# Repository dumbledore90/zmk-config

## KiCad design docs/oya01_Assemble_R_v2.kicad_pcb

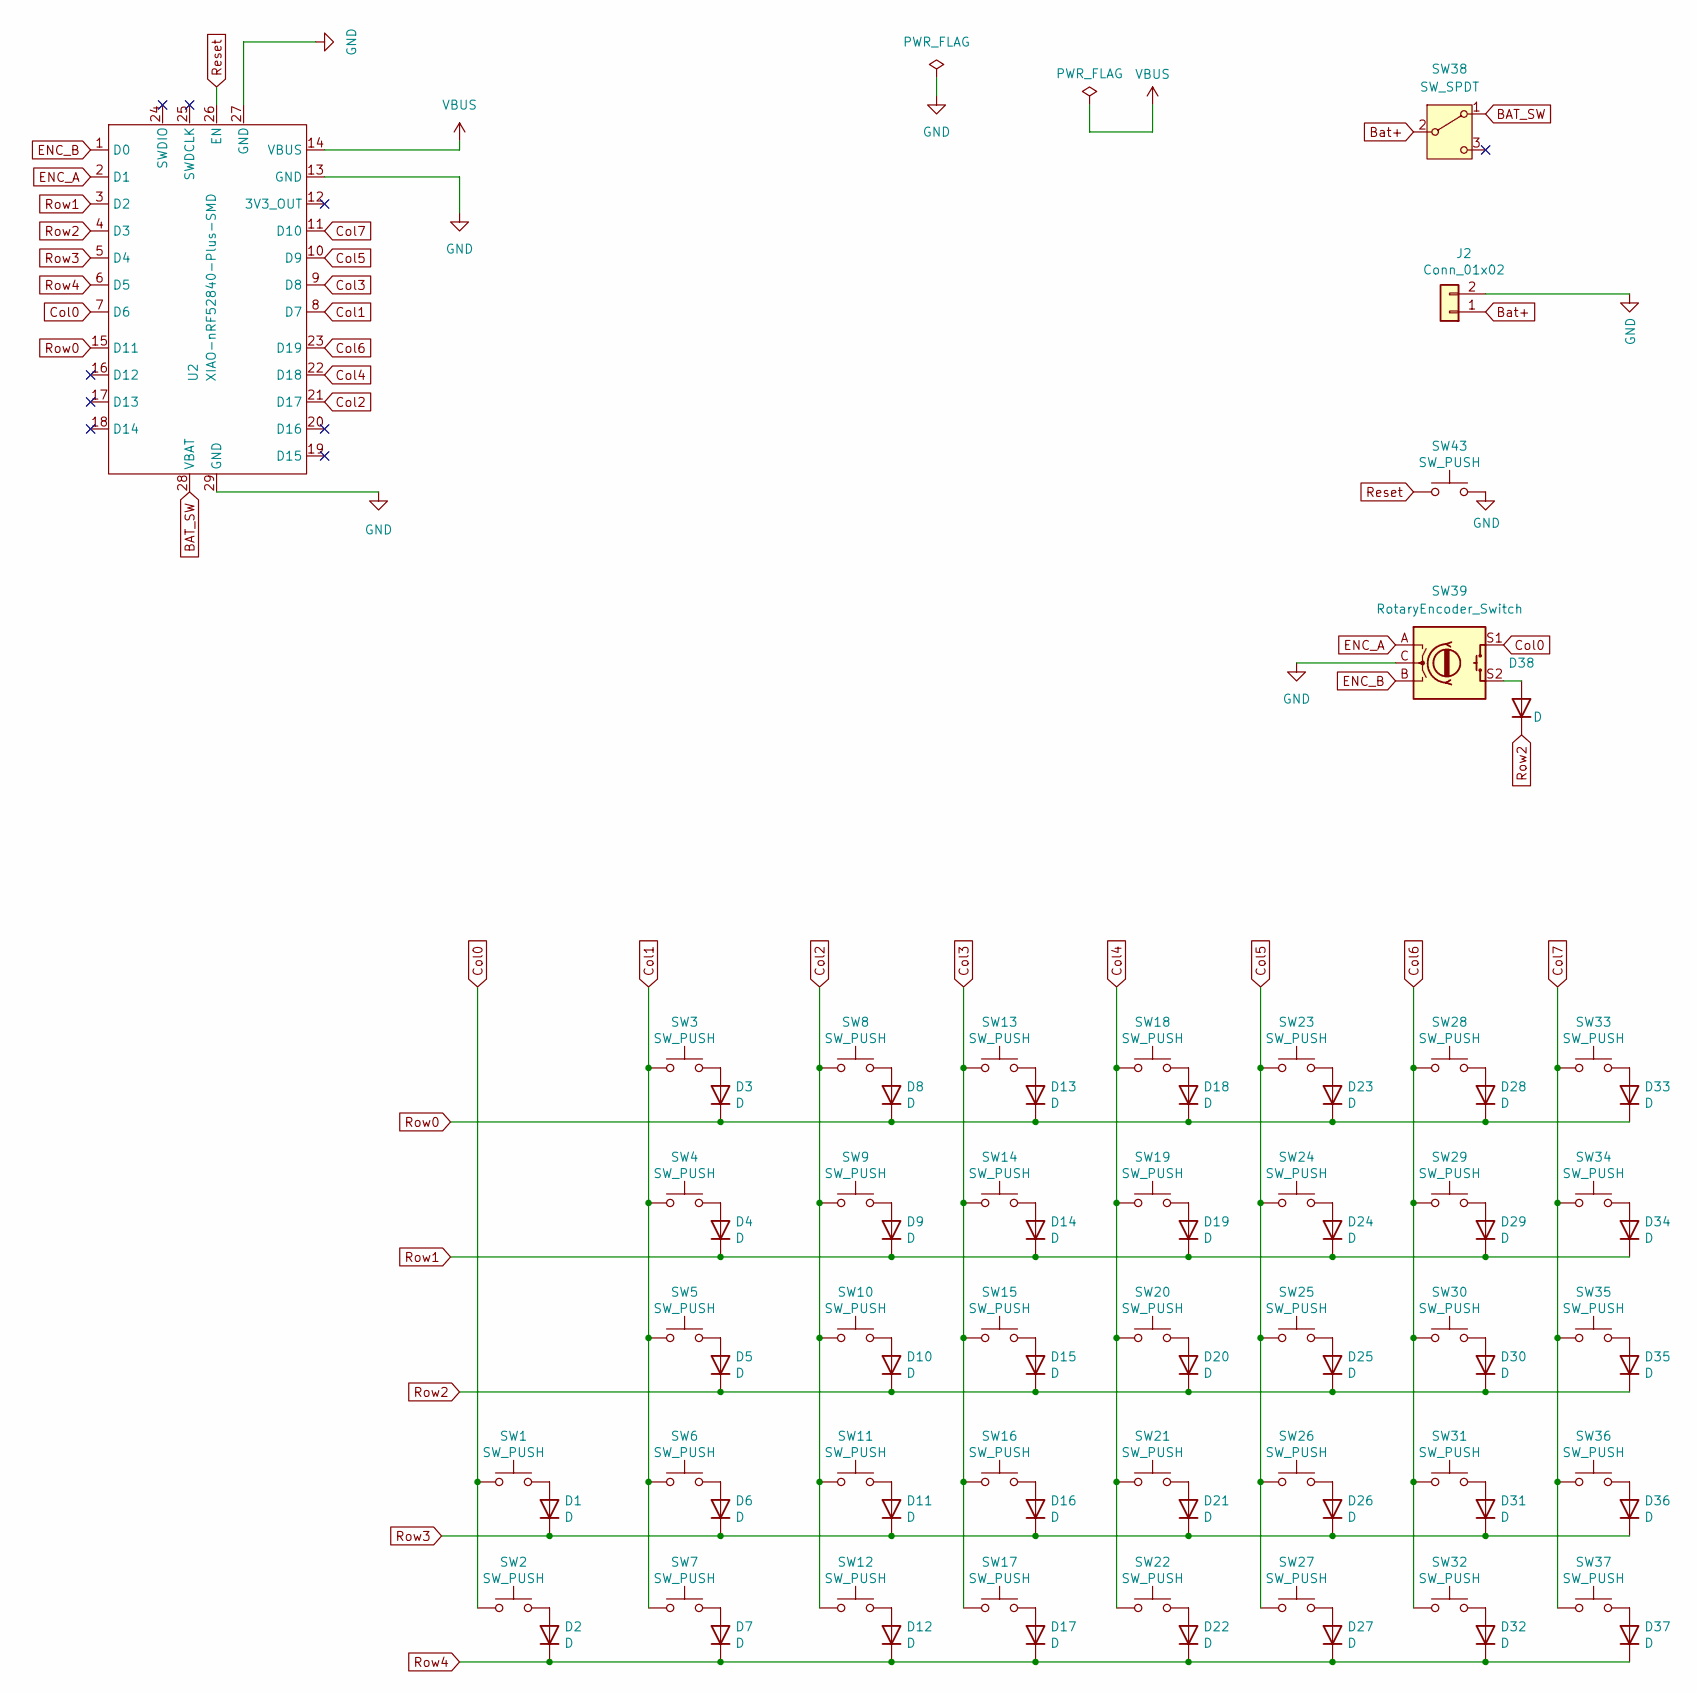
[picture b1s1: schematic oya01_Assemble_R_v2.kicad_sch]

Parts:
D1, D2, D3, D4, D5, D6, D7, D8, D9, D10, D11, D12, D13, D14, D15, D16, D17, D18, D19, D20, D21, D22, D23, D24, D25, D26, D27, D28, D29, D30, D31, D32, D33, D34, D35, D36, D37, D38: D; D_SOD-123
J2: Conn_01x02; JST_PH_S2B-PH-K_1x02_P2.00mm_Horizontal
SW1, SW2, SW3, SW4, SW5, SW6, SW7, SW8, SW9, SW10, SW11, SW12, SW13, SW14, SW15, SW16, SW17, SW18, SW19, SW20, SW21, SW22, SW23, SW24, SW25, SW26, SW27, SW28, SW29, SW30, SW31, SW32, SW33, SW34, SW35, SW36, SW37: SW_PUSH; Kailh_Choc_V1_Hotswap_thin_via
SW38: SW_SPDT; TGSW_MSK-12D19
SW39: RotaryEncoder_Switch; RotaryEncoder_EC12E
SW43: SW_PUSH; ResetSW
U2: XIAO-nRF52840-Plus-SMD

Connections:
BAT_SW: SW38.1 (A), U2.28 (VBAT)
Bat+: J2.1, SW38.2 (B)
Col0: SW1.1, SW2.1, SW39.S1, U2.7 (D6)
Col1: SW3.1, SW4.1, SW5.1, SW6.1, SW7.1, U2.8 (D7)
Col2: SW8.1, SW9.1, SW10.1, SW11.1, SW12.1, U2.21 (D17)
Col3: SW13.1, SW14.1, SW15.1, SW16.1, SW17.1, U2.9 (D8)
Col4: SW18.1, SW19.1, SW20.1, SW21.1, SW22.1, U2.22 (D18)
Col5: SW23.1, SW24.1, SW25.1, SW26.1, SW27.1, U2.10 (D9)
Col6: SW28.1, SW29.1, SW30.1, SW31.1, SW32.1, U2.23 (D19)
Col7: SW33.1, SW34.1, SW35.1, SW36.1, SW37.1, U2.11 (D10)
ENC_A: SW39.A, U2.2 (D1)
ENC_B: SW39.B, U2.1 (D0)
GND: J2.2, SW39.C, SW43.2, U2.13 (GND), U2.27 (GND), U2.29 (GND)
unnamed: D1.2 (A), SW1.2
unnamed: D2.2 (A), SW2.2
unnamed: D3.2 (A), SW3.2
unnamed: D4.2 (A), SW4.2
unnamed: D5.2 (A), SW5.2
unnamed: D6.2 (A), SW6.2
unnamed: D7.2 (A), SW7.2
unnamed: D8.2 (A), SW8.2
unnamed: D9.2 (A), SW9.2
unnamed: D10.2 (A), SW10.2
unnamed: D11.2 (A), SW11.2
unnamed: D12.2 (A), SW12.2
unnamed: D13.2 (A), SW13.2
unnamed: D14.2 (A), SW14.2
unnamed: D15.2 (A), SW15.2
unnamed: D16.2 (A), SW16.2
unnamed: D17.2 (A), SW17.2
unnamed: D18.2 (A), SW18.2
unnamed: D19.2 (A), SW19.2
unnamed: D20.2 (A), SW20.2
unnamed: D21.2 (A), SW21.2
unnamed: D22.2 (A), SW22.2
unnamed: D23.2 (A), SW23.2
unnamed: D24.2 (A), SW24.2
unnamed: D25.2 (A), SW25.2
unnamed: D26.2 (A), SW26.2
unnamed: D27.2 (A), SW27.2
unnamed: D28.2 (A), SW28.2
unnamed: D29.2 (A), SW29.2
unnamed: D30.2 (A), SW30.2
unnamed: D31.2 (A), SW31.2
unnamed: D32.2 (A), SW32.2
unnamed: D33.2 (A), SW33.2
unnamed: D34.2 (A), SW34.2
unnamed: D35.2 (A), SW35.2
unnamed: D36.2 (A), SW36.2
unnamed: D37.2 (A), SW37.2
unnamed: D38.2 (A), SW39.S2
Reset: SW43.1, U2.26 (EN)
Row0: D3.1 (K), D8.1 (K), D13.1 (K), D18.1 (K), D23.1 (K), D28.1 (K), D33.1 (K), U2.15 (D11)
Row1: D4.1 (K), D9.1 (K), D14.1 (K), D19.1 (K), D24.1 (K), D29.1 (K), D34.1 (K), U2.3 (D2)
Row2: D5.1 (K), D10.1 (K), D15.1 (K), D20.1 (K), D25.1 (K), D30.1 (K), D35.1 (K), D38.1 (K), U2.4 (D3)
Row3: D1.1 (K), D6.1 (K), D11.1 (K), D16.1 (K), D21.1 (K), D26.1 (K), D31.1 (K), D36.1 (K), U2.5 (D4)
Row4: D2.1 (K), D7.1 (K), D12.1 (K), D17.1 (K), D22.1 (K), D27.1 (K), D32.1 (K), D37.1 (K), U2.6 (D5)
VBUS: U2.14 (VBUS)

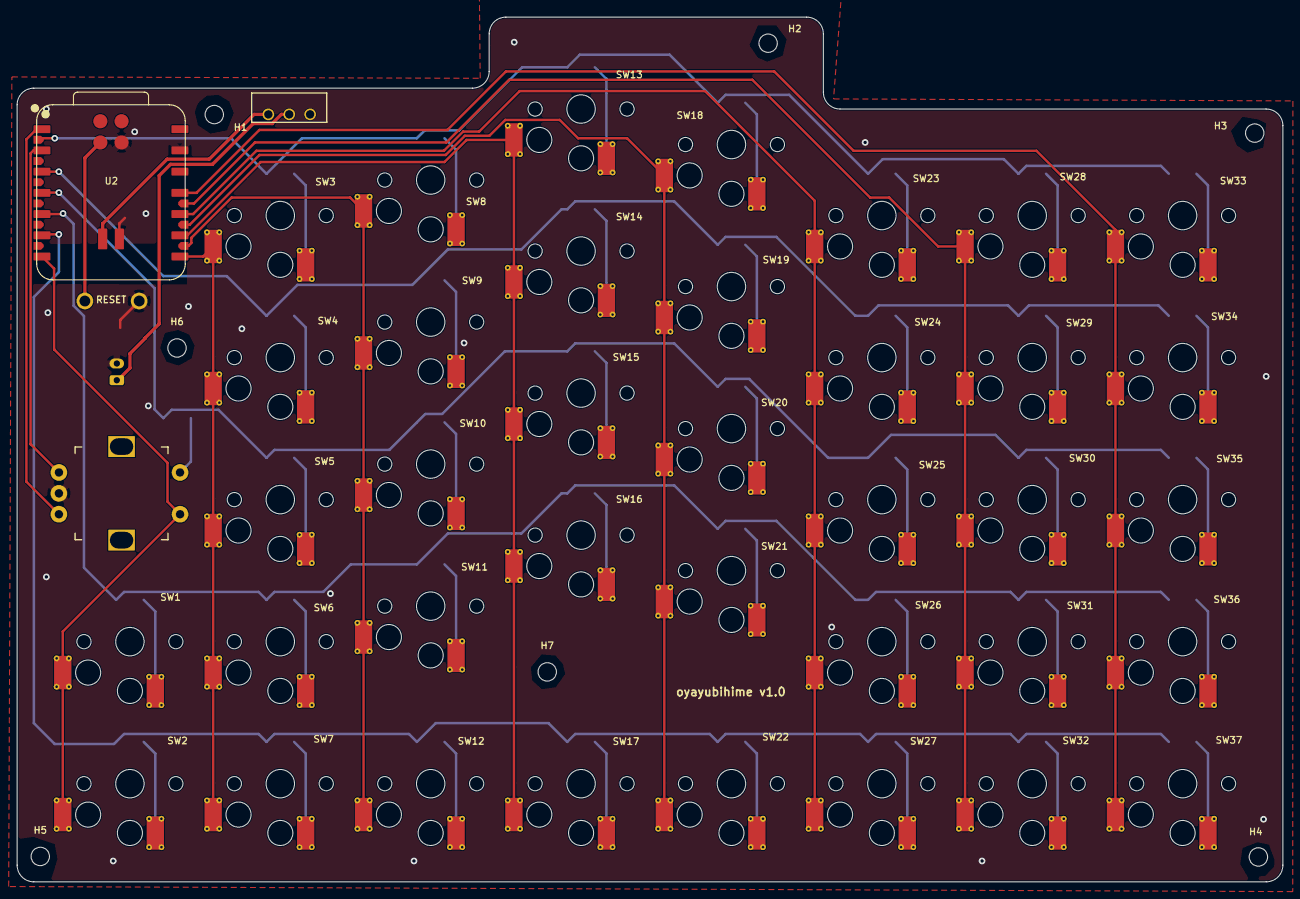
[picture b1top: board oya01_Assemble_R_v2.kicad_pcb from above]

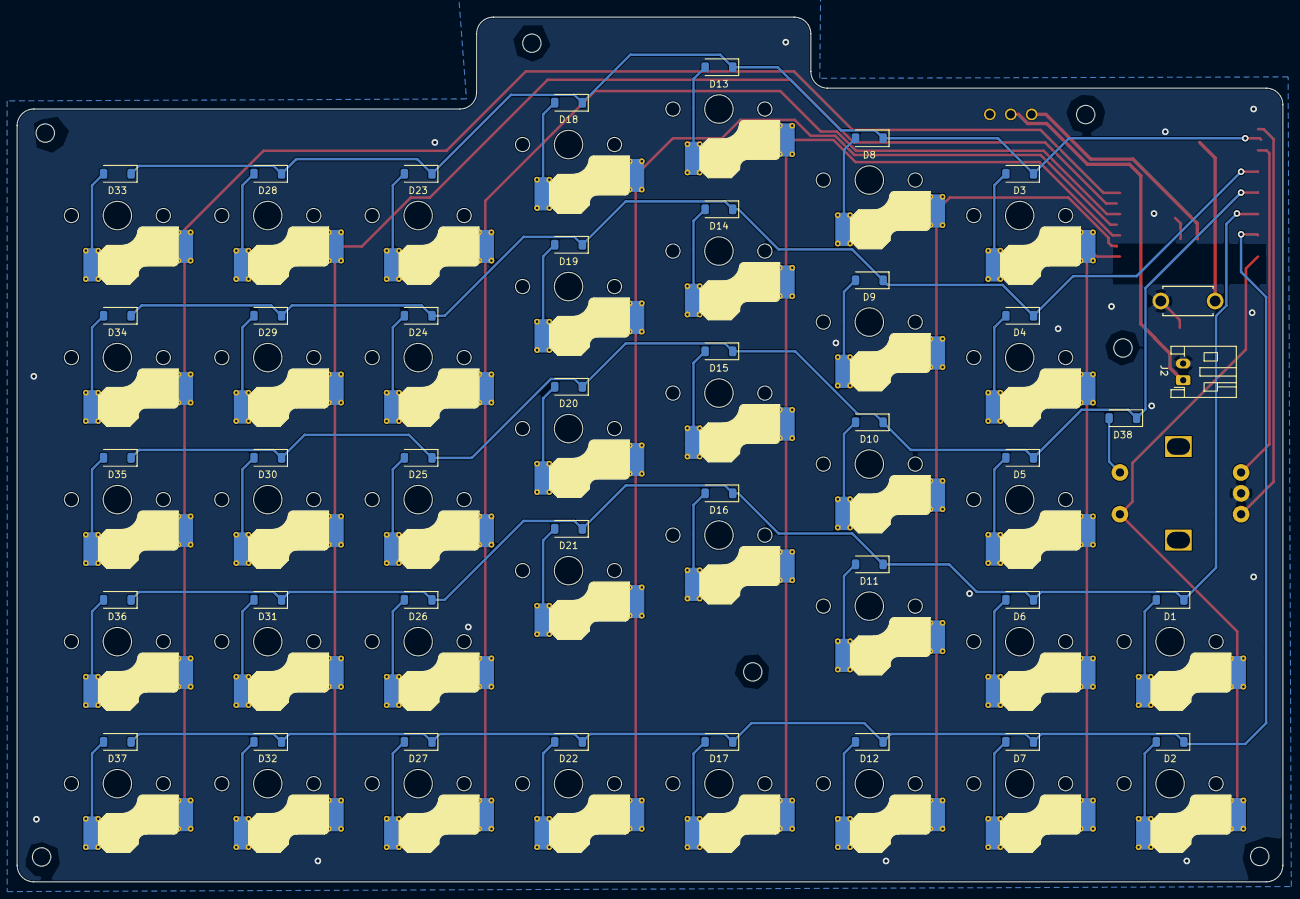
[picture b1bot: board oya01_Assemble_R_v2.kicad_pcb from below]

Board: 2 copper layers, 151.5 x 103.5 mm, 87 parts (39 on the bottom side), 57 nets.

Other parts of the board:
H1, H2, H3, H4, H5, H6, H7: MountingHole_2.2mm_M2

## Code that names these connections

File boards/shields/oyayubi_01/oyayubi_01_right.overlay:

#include "oyayubi_01.dtsi"

// 右手 (peripheral) の GPIO アサイン
// ピン番号の出典: docs/xiao_gpio_map_v2.md
// &xiao_d は D11 以降未定義のため使わず、全ピン &gpio0/&gpio1 で直接指定

&default_transform {
    col-offset = <7>;  // 右 Col0 → unified col 7、右 Col7 → unified col 14
};

&kscan {
    row-gpios =
        <&gpio0 15 (GPIO_ACTIVE_HIGH | GPIO_PULL_DOWN)>,  // Row0 / D11 / P0.15
        <&gpio0 28 (GPIO_ACTIVE_HIGH | GPIO_PULL_DOWN)>,  // Row1 / D2  / P0.28
        <&gpio0 29 (GPIO_ACTIVE_HIGH | GPIO_PULL_DOWN)>,  // Row2 / D3  / P0.29
        <&gpio0 4  (GPIO_ACTIVE_HIGH | GPIO_PULL_DOWN)>,  // Row3 / D4  / P0.04
        <&gpio0 5  (GPIO_ACTIVE_HIGH | GPIO_PULL_DOWN)>;  // Row4 / D5  / P0.05

    col-gpios =
        <&gpio1 11 GPIO_ACTIVE_HIGH>,  // Col0 / D6  / P1.11
        <&gpio1 12 GPIO_ACTIVE_HIGH>,  // Col1 / D7  / P1.12
        <&gpio1 3  GPIO_ACTIVE_HIGH>,  // Col2 / D17 / P1.03  // TODO: 要実機検証（D17/D19 逆の可能性）
        <&gpio1 13 GPIO_ACTIVE_HIGH>,  // Col3 / D8  / P1.13
        <&gpio1 5  GPIO_ACTIVE_HIGH>,  // Col4 / D18 / P1.05
        <&gpio1 14 GPIO_ACTIVE_HIGH>,  // Col5 / D9  / P1.14
        <&gpio1 7  GPIO_ACTIVE_HIGH>,  // Col6 / D19 / P1.07  // TODO: 要実機検証（D17/D19 逆の可能性）
        <&gpio1 15 GPIO_ACTIVE_HIGH>;  // Col7 / D10 / P1.15
};

/ {
    // EC11 互換エンコーダ（ENC_A=D1/P0.03, ENC_B=D0/P0.02）
    // プッシュスイッチは Row2 × Col0 のマトリクスに入る（D38 経由）
    encoder: encoder {
        compatible = "alps,ec11";
        a-gpios = <&gpio0 3 (GPIO_ACTIVE_HIGH | GPIO_PULL_UP)>;  // ENC_A / D1 / P0.03
        b-gpios = <&gpio0 2 (GPIO_ACTIVE_HIGH | GPIO_PULL_UP)>;  // ENC_B / D0 / P0.02
        steps = <80>;  // 20 detents × 4 pulses/detent
    };

    // センサー登録（keymap の sensor-bindings と対応）
    sensors: sensors {
        compatible = "zmk,keymap-sensors";
        sensors = <&encoder>;
        triggers-per-rotation = <20>;  // 1 クリック = 1 イベント
    };
};
